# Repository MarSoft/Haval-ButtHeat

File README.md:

Butt Heat Controller
====================

Custom controller for Haval Dargo's seat heaters (and A/C in the future).

Hardware and connections
------------------------

This shall run on ESP32C3 board with TJA1050 (5V power supply) or similar module
Connect to 5V supply (or more likely IGN 12V) and BD-CAN-1 (see the schematics).

Controls: two rotary encoders (left and right A/C control, click -> seat heat control, long press -> seat memory recall)
and SSD1306 0.91" 128x32 tiny display which fits above the "MODE" knob in the car.

Power (IGN) connection:
H08/P08 pin29 wire A239 R-Y, IG1, fuse F122 10A
(H08/P08 pin32 wire A221 <s> ACC?)

BD-CAN-1 connection:
H104/P104 pin1,pin2 (Green-Red, Blue-Black)

"Montage map" from some alarm systems vendor: https://integrator.tecel.ru/api/attachment/181021
(it describes how to access the connectors under left kick panel)

Thingiverse project with a better description: https://www.thingiverse.com/thing:7438047

Logic
-----

1. Listen for 2D1#00xx000000000000 messages, where `xx` is a heater status byte. They come like 10 per second.
2. Control: send 36D#00yy200000000040, where yy is a heater status *with offset*.
3. After sending a message, do not change internal state for external messages for e.g. 500ms, so that the machine will have time to react.
4. Bus error state: show "spinner" with LEDs.

Tasks:

1. Bus RX. Also responsible for bus reconnects?
2. Bus TX. Not sure if it is really required though.
3. Router task. Gets events from rotary-encoder queue (the driver uses single queue for everything) and routes them to the respective tasks.
4. Button and rotary encoders input. Also sends CAN msgs? One task per button and per encoder. Each task gets events from both input and can and is responsible for interpreting them and notifying the display.
5. Display output task.

Communication:
RX -> Button (separate task per each)
Button -> TX (or just send directly?)
Button -> Display
RX -> Display (error state)

Types:
- ac_temp_t (LO, HI, unknown, half-degrees)
- butt_temp_t (0, 1, 2, 3, unknown)

States:
1. Loading, or bus error. Spinner. Denoted by spinner_sem taken by non-LED task.
2. Normal: show info based on led_from_can_queue.
3. Input (250ms after button press): show info based on led_from_btn_queue

What can go wrong
-----------------

The PCB schematics' maximum input voltage is 18V. Anything below is okay — so jump starting the car should not damage this device.
What happens if this voltage is exceeded for some reason? At 20-26V, D3 will die, together with a fuse. Recovery: replace D3 and fuse.
Above 40V: U4 and C3 may also die.

CAN bus. This device is connected to BD-CAN-1 — one of the 6 CAN buses in Haval Dargo. PCB version uses TJA1051T/3 chip — it has a built-in timeout, so even if MCU hangs, CAN bus is never held busy.
If another CAN chip is used in your build, *and* MCU hangs in CAN-low condition (never occured on the prototype) — in the worst case BD-CAN-1 will become irresponsible. What does it mean for the car? This bus is used for the following devices, which will stop communicating with each other:
- Multimedia system
- Front doors (buttons)
- Front seats (seat moving buttons)
- Wireless phone charger
- Climate control system
- KBCM module
- Most noticeable: multi-switch under steering wheel

Note: nothing critical (steering, brake, ignition) is affected.

How to fix this if it ever happens? Power cycle will most likely help. If it doesn't then disconnect the device. That's why the device should be connected with a detachable connector rather than wired in directly.

Firmware updates
----------------

Two ways, neither needs an ESP-IDF install:

**OTA (in the car):** hold the left knob's button while switching ignition on.
The display shows an AP name, a password and `192.168.4.1`. Join the
`ButtHeat-OTA` Wi-Fi from a phone or laptop (password is on the display), open
<http://192.168.4.1> and upload the `buttheat.bin` from the
[releases page](https://github.com/MarSoft/Haval-ButtHeat/releases).
The page is served by the device, so the phone needs no internet during the
upload — but download the `.bin` beforehand (Android keeps LTE alive on this
AP; iPhones go offline). Power-cycle to leave OTA mode.

**USB (first flash / recovery):** open the
[web installer](https://marsoft.github.io/Haval-ButtHeat/) in desktop
Chrome/Edge/Firefox or Chrome on Android, connect the board over USB, click
Install. iOS browsers have no USB-serial access — use OTA there. The installer
reflashes bootloader + partition table + app in one go.

Safety net: an update is written to the inactive slot, and the bootloader
rolls back to the previous image unless the new one runs for 5 seconds after a
normal boot. Every release contains the OTA code itself, so an update can't
lock you out of updating again. Versioning: `v0.9.x` pre-release, `v1.0.0` =
first hardware/PCB generation (prototype hardware = `v0.1`).

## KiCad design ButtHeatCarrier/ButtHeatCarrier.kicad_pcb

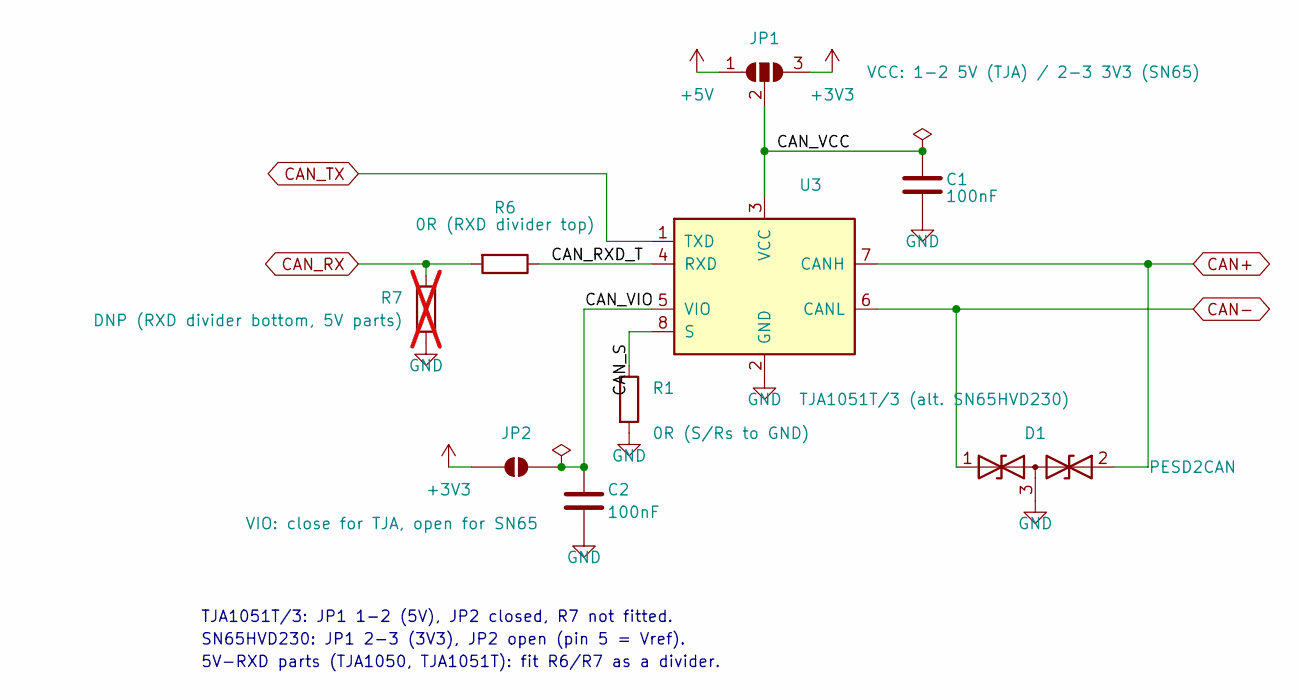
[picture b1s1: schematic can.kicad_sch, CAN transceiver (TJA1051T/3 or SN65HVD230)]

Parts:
C1, C2: 100nF; C_0603_1608Metric
D1: PESD2CAN; SOT-23
JP1: VCC: 1-2 5V (TJA) / 2-3 3V3 (SN65); SolderJumper-3_P1.3mm_Open_RoundedPad1.0x1.5mm
JP2: VIO: close for TJA, open for SN65; SolderJumper-2_P1.3mm_Open_RoundedPad1.0x1.5mm
R1: 0R (S/Rs to GND); R_0603_1608Metric
R6: 0R (RXD divider top); R_0603_1608Metric
R7: DNP (RXD divider bottom, 5V parts); R_0603_1608Metric; not fitted
U3: TJA1051T/3 (alt. SN65HVD230); SOIC-8_3.9x4.9mm_P1.27mm

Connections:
+3V3: JP1.3 (B), JP2.2 (B); also elsewhere on the board
+5V: JP1.1 (A); also elsewhere on the board
/CAN/CAN_RXD_T: R6.1, U3.4 (RXD)
/CAN/CAN_S: R1.1, U3.8 (S)
/CAN/CAN_VCC: C1.1, JP1.2 (C), U3.3 (VCC)
/CAN/CAN_VIO: C2.1, JP2.1 (A), U3.5 (VIO)
CAN+: D1.2 (A2), U3.7 (CANH); also elsewhere on the board
CAN-: D1.1 (A1), U3.6 (CANL); also elsewhere on the board
CAN_RX: R6.2, R7.1; also elsewhere on the board
CAN_TX: U3.1 (TXD); also elsewhere on the board
GND: C1.2, C2.2, D1.3 (common), R1.2, R7.2, U3.2 (GND); also elsewhere on the board

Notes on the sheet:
TJA1051T/3: JP1 1-2 (5V), JP2 closed, R7 not fitted.
SN65HVD230: JP1 2-3 (3V3), JP2 open (pin 5 = Vref).
5V-RXD parts (TJA1050, TJA1051T): fit R6/R7 as a divider.

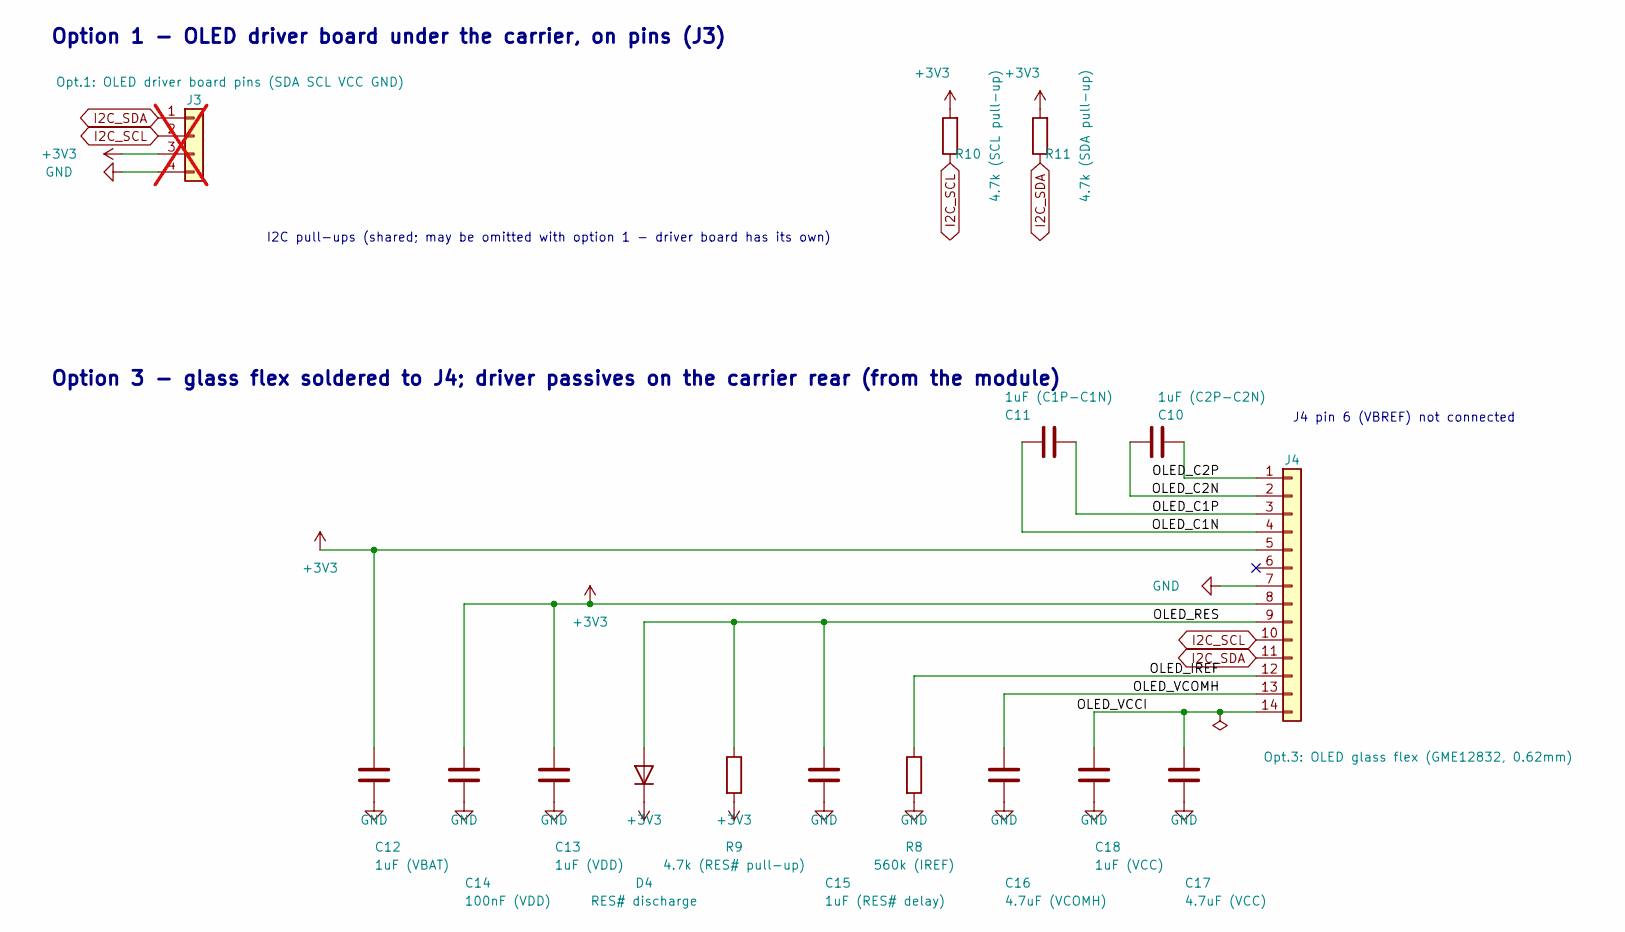
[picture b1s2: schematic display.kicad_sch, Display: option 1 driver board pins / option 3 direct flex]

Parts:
C10: 1uF (C2P-C2N); C_0603_1608Metric
C11: 1uF (C1P-C1N); C_0603_1608Metric
C12: 1uF (VBAT); C_0603_1608Metric
C13: 1uF (VDD); C_0603_1608Metric
C14: 100nF (VDD); C_0603_1608Metric
C15: 1uF (RES# delay); C_0603_1608Metric
C16: 4.7uF (VCOMH); C_0603_1608Metric
C17: 4.7uF (VCC); C_0603_1608Metric
C18: 1uF (VCC); C_0603_1608Metric
D4: RES# discharge; D_SOD-523
J3: Opt.1: OLED driver board pins (SDA SCL VCC GND); PinHeader_1x04_P2.54mm_Vertical; not fitted
J4: Opt.3: OLED glass flex (GME12832, 0.62mm); OLED_FPC_14P_P0.62mm
R8: 560k (IREF); R_0603_1608Metric
R9: 4.7k (RES# pull-up); R_0603_1608Metric
R10: 4.7k (SCL pull-up); R_0603_1608Metric
R11: 4.7k (SDA pull-up); R_0603_1608Metric

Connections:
+3V3: C12.1, C13.1, C14.1, D4.1 (K), J3.3, J4.5, J4.8, R9.2, R10.2, R11.2; also elsewhere on the board
/Display/OLED_C1N: C11.2, J4.4
/Display/OLED_C1P: C11.1, J4.3
/Display/OLED_C2N: C10.2, J4.2
/Display/OLED_C2P: C10.1, J4.1
/Display/OLED_IREF: J4.12, R8.1
/Display/OLED_RES: C15.1, D4.2 (A), J4.9, R9.1
/Display/OLED_VCCI: C17.1, C18.1, J4.14
/Display/OLED_VCOMH: C16.1, J4.13
GND: C12.2, C13.2, C14.2, C15.2, C16.2, C17.2, C18.2, J3.4, J4.7, R8.2; also elsewhere on the board
I2C_SCL: J3.2, J4.10, R10.1; also elsewhere on the board
I2C_SDA: J3.1, J4.11, R11.1; also elsewhere on the board

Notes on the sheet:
J4 pin 6 (VBREF) not connected
Option 3 - glass flex soldered to J4; driver passives on the carrier rear (from the module)
Option 1 - OLED driver board under the carrier, on pins (J3)
I2C pull-ups (shared; may be omitted with option 1 - driver board has its own)

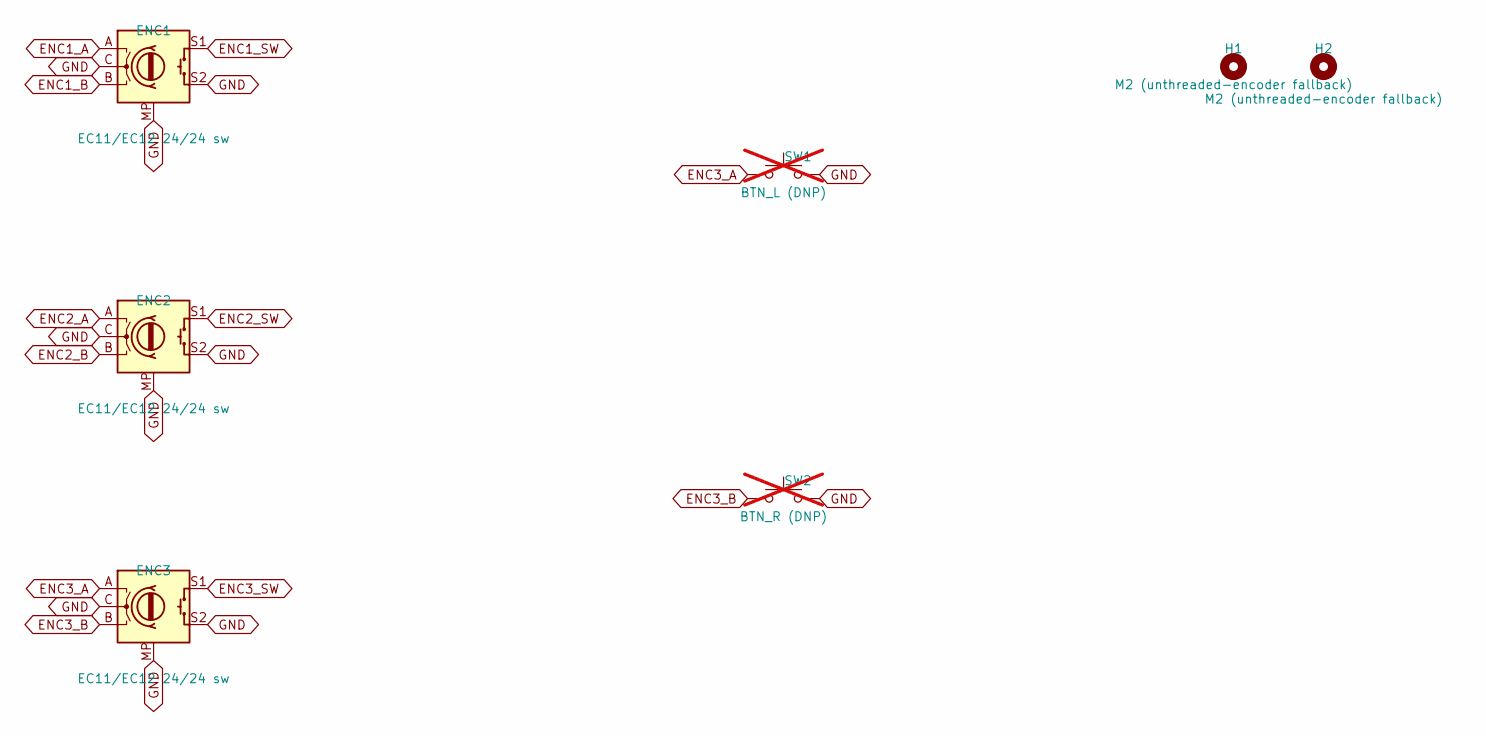
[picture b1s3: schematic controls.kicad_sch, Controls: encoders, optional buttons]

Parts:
ENC1, ENC2, ENC3: EC11/EC12 24/24 sw; RotaryEncoder_EC11_EC12-Switch_Vertical_H20mm
H1, H2: M2 (unthreaded-encoder fallback); MountingHole_2.2mm_M2
SW1: BTN_L (DNP); SW_Tactile_6x6_THT_SMD; not fitted
SW2: BTN_R (DNP); SW_Tactile_6x6_THT_SMD; not fitted

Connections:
ENC1_A: ENC1.A; also elsewhere on the board
ENC1_B: ENC1.B; also elsewhere on the board
ENC1_SW: ENC1.S1; also elsewhere on the board
ENC2_A: ENC2.A; also elsewhere on the board
ENC2_B: ENC2.B; also elsewhere on the board
ENC2_SW: ENC2.S1; also elsewhere on the board
ENC3_A: ENC3.A, SW1.1; also elsewhere on the board
ENC3_B: ENC3.B, SW2.1; also elsewhere on the board
ENC3_SW: ENC3.S1; also elsewhere on the board
GND: ENC1.C, ENC1.MP, ENC1.S2, ENC2.C, ENC2.MP, ENC2.S2, ENC3.C, ENC3.MP, ENC3.S2, SW1.2, SW2.2; also elsewhere on the board

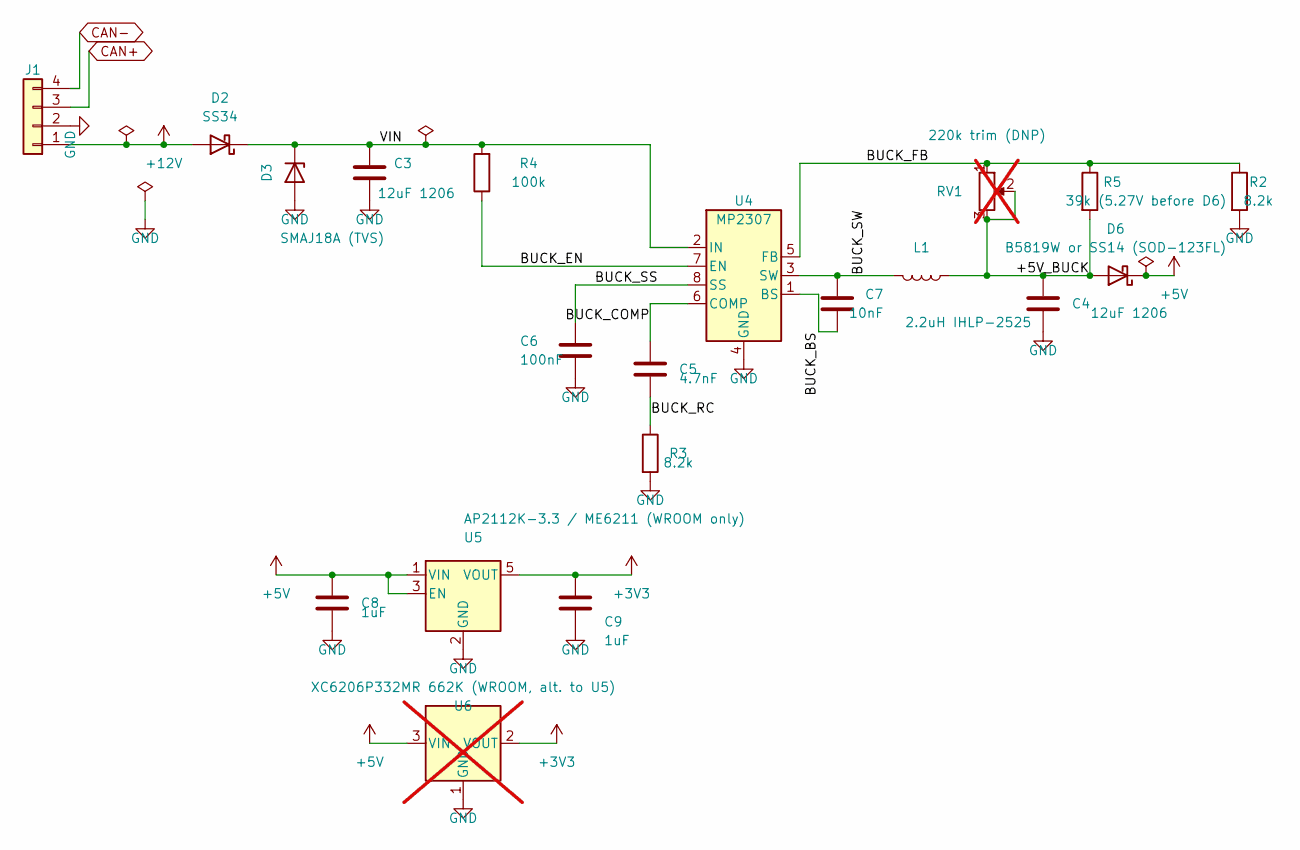
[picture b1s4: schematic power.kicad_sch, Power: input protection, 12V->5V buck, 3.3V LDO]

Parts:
C3, C4: 12uF 1206; C_1206_3216Metric
C5: 4.7nF; C_0603_1608Metric
C6: 100nF; C_0603_1608Metric
C7: 10nF; C_0603_1608Metric
C8, C9: 1uF; C_0603_1608Metric
D2: SS34; D_SMA
D3: SMAJ18A (TVS); D_SMA
D6: B5819W or SS14 (SOD-123FL); D_SOD-123
J1: JST-ZH 4p (12V GND CANH CANL); JST_ZH_B4B-ZR_1x04_P1.50mm_Vertical
L1: 2.2uH IHLP-2525; L_Vishay_IHLP-2525
R2, R3: 8.2k; R_0603_1608Metric
R4: 100k; R_0603_1608Metric
R5: 39k (5.27V before D6); R_0603_1608Metric
RV1: 220k trim (DNP); Potentiometer_Bourns_TC33X_Vertical; not fitted
U4: MP2307; SOIC-8_3.9x4.9mm_P1.27mm
U5: AP2112K-3.3 / ME6211 (WROOM only); SOT-23-5
U6: XC6206P332MR 662K (WROOM, alt. to U5); SOT-23; not fitted

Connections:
+3V3: C9.1, U5.5 (VOUT), U6.2 (VOUT); also elsewhere on the board
+5V: C8.1, D6.1 (K), U5.1 (VIN), U5.3 (EN), U6.3 (VIN); also elsewhere on the board
+12V: D2.2 (A), J1.1
/Power/+5V_BUCK: C4.1, D6.2 (A), L1.1, R5.2, RV1.2, RV1.3
/Power/BUCK_BS: C7.1, U4.1 (BS)
/Power/BUCK_COMP: C5.1, U4.6 (COMP)
/Power/BUCK_EN: R4.1, U4.7 (EN)
/Power/BUCK_FB: R2.1, R5.1, RV1.1, U4.5 (FB)
/Power/BUCK_RC: C5.2, R3.1
/Power/BUCK_SS: C6.1, U4.8 (SS)
/Power/BUCK_SW: C7.2, L1.2, U4.3 (SW)
/Power/VIN: C3.1, D2.1 (K), D3.1 (K), R4.2, U4.2 (IN)
CAN+: J1.3; also elsewhere on the board
CAN-: J1.4; also elsewhere on the board
GND: C3.2, C4.2, C6.2, C8.2, C9.2, D3.2 (A), J1.2, R2.2, R3.2, U4.4 (GND), U5.2 (GND), U6.1 (GND); also elsewhere on the board

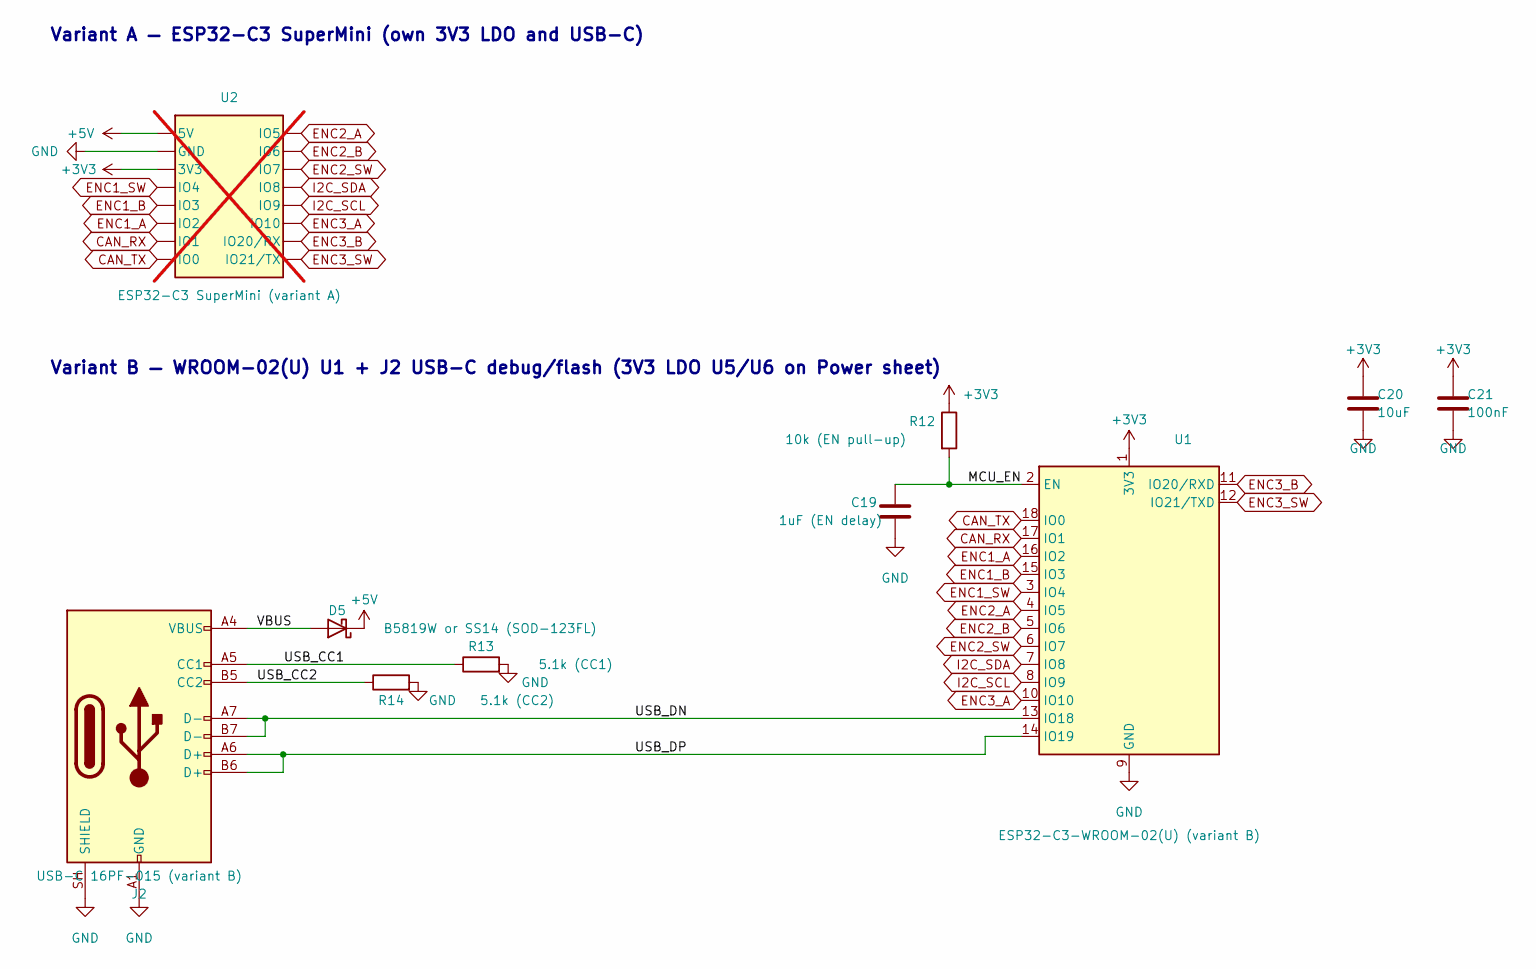
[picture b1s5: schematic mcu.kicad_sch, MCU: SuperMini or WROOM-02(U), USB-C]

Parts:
C19: 1uF (EN delay); C_0603_1608Metric
C20: 10uF; C_0805_2012Metric
C21: 100nF; C_0603_1608Metric
D5: B5819W or SS14 (SOD-123FL); D_SOD-123
J2: USB-C 16PF-015 (variant B); USB_C_16PF-015
R12: 10k (EN pull-up); R_0603_1608Metric
R13: 5.1k (CC1); R_0603_1608Metric
R14: 5.1k (CC2); R_0603_1608Metric
U1: ESP32-C3-WROOM-02(U) (variant B); ESP32-C3-WROOM-02_Via0.3
U2: ESP32-C3 SuperMini (variant A); ESP32-C3-SuperMini; not fitted

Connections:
+3V3: C20.1, C21.1, R12.1, U1.1 (3V3), U2.3V3; also elsewhere on the board
+5V: D5.1 (K), U2.5V; also elsewhere on the board
/MCU/MCU_EN: C19.1, R12.2, U1.2 (EN)
/MCU/USB_CC1: J2.A5 (CC1), R13.1
/MCU/USB_CC2: J2.B5 (CC2), R14.1
/MCU/USB_DN: J2.A7 (D-), J2.B7 (D-), U1.13 (IO18)
/MCU/USB_DP: J2.A6 (D+), J2.B6 (D+), U1.14 (IO19)
/MCU/VBUS: D5.2 (A), J2.A4 (VBUS), J2.A9 (VBUS), J2.B4 (VBUS), J2.B9 (VBUS)
CAN_RX: U1.17 (IO1), U2.IO1; also elsewhere on the board
CAN_TX: U1.18 (IO0), U2.IO0; also elsewhere on the board
ENC1_A: U1.16 (IO2), U2.IO2; also elsewhere on the board
ENC1_B: U1.15 (IO3), U2.IO3; also elsewhere on the board
ENC1_SW: U1.3 (IO4), U2.IO4; also elsewhere on the board
ENC2_A: U1.4 (IO5), U2.IO5; also elsewhere on the board
ENC2_B: U1.5 (IO6), U2.IO6; also elsewhere on the board
ENC2_SW: U1.6 (IO7), U2.IO7; also elsewhere on the board
ENC3_A: U1.10 (IO10), U2.IO10; also elsewhere on the board
ENC3_B: U1.11 (IO20/RXD), U2.IO20 (IO20/RX); also elsewhere on the board
ENC3_SW: U1.12 (IO21/TXD), U2.IO21 (IO21/TX); also elsewhere on the board
GND: C19.2, C20.2, C21.2, J2.A1 (GND), J2.A12 (GND), J2.B1 (GND), J2.B12 (GND), J2.SH (SHIELD), R13.2, R14.2, U1.9 (GND), U1.19 (GND), U2.GND; also elsewhere on the board
I2C_SCL: U1.8 (IO9), U2.IO9; also elsewhere on the board
I2C_SDA: U1.7 (IO8), U2.IO8; also elsewhere on the board

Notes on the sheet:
Variant A — ESP32-C3 SuperMini (own 3V3 LDO and USB-C)
Variant B — WROOM-02(U) U1 + J2 USB-C debug/flash (3V3 LDO U5/U6 on Power sheet)

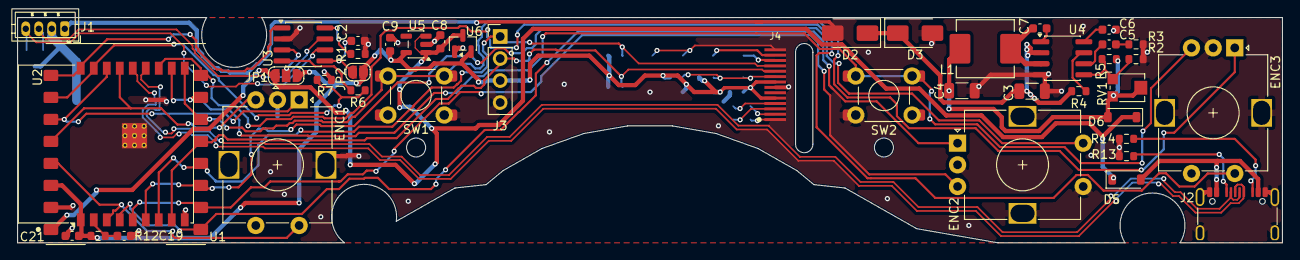
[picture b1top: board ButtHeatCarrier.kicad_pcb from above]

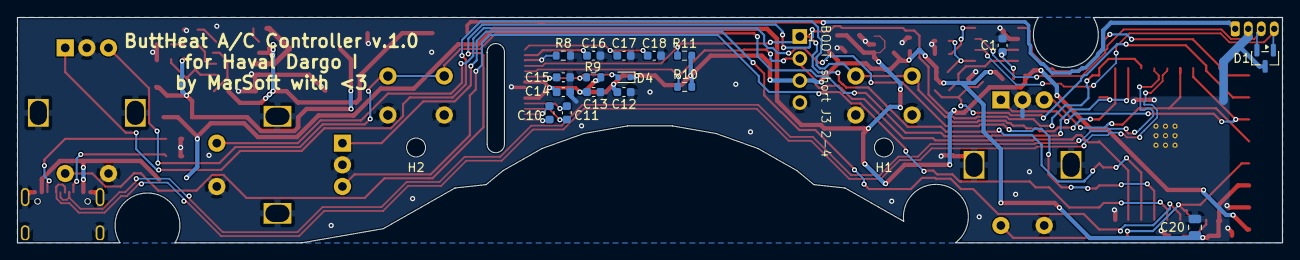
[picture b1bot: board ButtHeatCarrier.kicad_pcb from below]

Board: 2 copper layers, 146.0 x 26.0 mm, 62 parts (17 on the bottom side), 46 nets.
